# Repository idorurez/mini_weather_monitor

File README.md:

# Amefuriko — Mini Weather Monitor

After using a really crappy indoor temp and humidity monitor, I wanted to build one for myself to see if I could do better. This is the result. Is it better? I have no idea, but at least it also has a forecast I can trust, built the way I like.

## What it does

* Indoor temperature (°F), humidity, and pressure from a BME280, refreshed every 60 seconds
* Date and time, synced over NTP
* Two-day forecast from Weather Underground: today and tomorrow, with a big icon showing today's weather (sun, clouds, rain, etc.)
* Backlight that follows the room: a BH1750 ambient light sensor drives PWM with smooth ramping, no stepped jumps

## Hardware

* ESP32 devkit (ESP-WROOM-32)
* 4" 480x320 TFT, ST7796 over SPI, run in portrait (320x480)
* BME280 (temp / humidity / pressure) and BH1750 (ambient light) on I2C
* Micro SD card on its own VSPI bus
* Custom PCB and schematic in `pcb/` (KiCad), 3D-printed stand/case models in `model/` (SolidWorks)

Pin map lives in `src/User_Setup.h`. TFT on MOSI 13 / SCLK 14 / CS 15 / DC 26 / RST 32, backlight on GPIO 4 (PWM). SD on VSPI: MOSI 23 / MISO 19 / SCLK 18 / CS 5.

## SD card contents

Everything in `sdcard/` goes on the card root:

* `kozgoprobold*.vlw` — Kozuka Gothic Bold smooth fonts, the UI typeface
* `*_120x120.jpg` — weather icons, named by Weather Underground icon code
* `weather.cfg` — your secrets and location (below). Not in the repo on purpose.

## Configuration

`/weather.cfg` on the SD card, JSON:

```json
{
  "wu_api_key": "your weather underground key",
  "zip": "94070",
  "station_id": "",
  "WIFI": { "hostname": "yokai", "ssid": "your-ssid", "pass": "your-password" },
  "LOCATION": { "latitude": "37.50", "longitude": "-122.34" }
}
```

## Build and flash

PlatformIO project (`platformio.ini` targets `esp32dev`, Arduino framework). Build and upload from VS Code with PlatformIO, or:

```
pio run -t upload
```

Serial monitor at 115200 baud.

## Layout

* `src/` — firmware
* `pcb/` — KiCad schematic and PCB
* `model/` — SolidWorks case/stand models plus a gcode
* `sdcard/` — fonts, weather icons, and config that live on the SD card

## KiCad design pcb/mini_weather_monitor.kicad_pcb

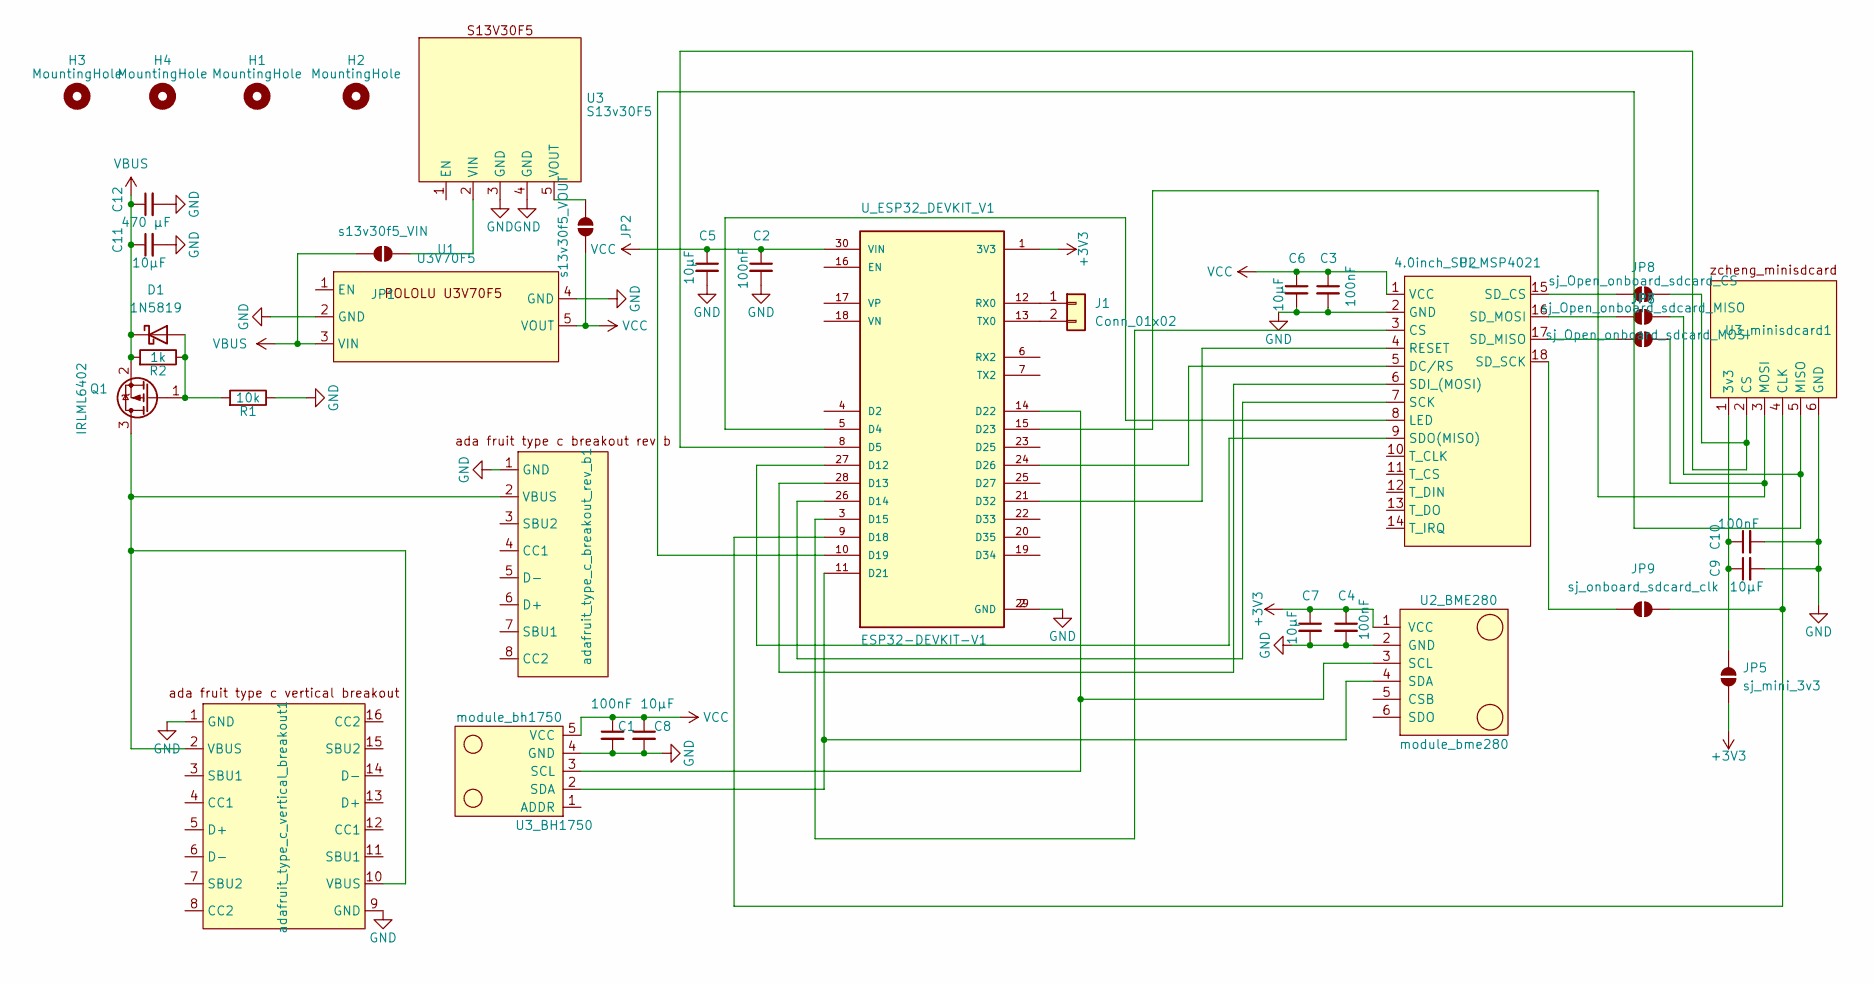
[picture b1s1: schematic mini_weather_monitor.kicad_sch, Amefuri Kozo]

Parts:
C1, C2, C3, C4, C10: 100nF; C_1206_3216Metric_Pad1.33x1.80mm_HandSolder
C5, C6, C7, C8, C9, C11: 10µF; C_1206_3216Metric_Pad1.33x1.80mm_HandSolder
C12: 470 µF; C_1206_3216Metric_Pad1.33x1.80mm_HandSolder
D1: 1N5819; D_SOD-123
H1, H2, H3, H4: MountingHole; MountingHole_2.2mm_M2
J1: Conn_01x02; PinHeader_1x02_P2.54mm_Vertical
JP1: s13v30f5_VIN; SolderJumper-2_P1.3mm_Open_RoundedPad1.0x1.5mm
JP2: s13v30f5_VOUT; SolderJumper-2_P1.3mm_Open_RoundedPad1.0x1.5mm
JP5: sj_mini_3v3; SolderJumper-2_P1.3mm_Open_RoundedPad1.0x1.5mm
JP6: sj_Open_onboard_sdcard_MOSI; SolderJumper-2_P1.3mm_Open_RoundedPad1.0x1.5mm
JP7: sj_Open_onboard_sdcard_MISO; SolderJumper-2_P1.3mm_Open_RoundedPad1.0x1.5mm
JP8: sj_Open_onboard_sdcard_CS; SolderJumper-2_P1.3mm_Open_RoundedPad1.0x1.5mm
JP9: sj_onboard_sdcard_clk; SolderJumper-2_P1.3mm_Open_RoundedPad1.0x1.5mm
Q1: IRLML6402; SOT-23
R1: 10k; R_1206_3216Metric
R2: 1k; R_1206_3216Metric
U1: U3V70F5; Pololu U3V70F5
U2: 4.0inch_SPI_MSP4021; 4.0inch_SPI
U2_BME280: module_bme280
U3: S13v30F5; pololu S13V30F5 step up step down
U3_BH1750: module_bh1750
U3_minisdcard1: zicheng_mini_sd_card_reader
U_ESP32_DEVKIT_V1: ESP32-DEVKIT-V1; MODULE_ESP32_DEVKIT_V1; PARTREV N/A
adafruit_type_c_breakout_rev_b1: Adafruit_USB_Type_C_Breakout_rev_B
adafruit_type_c_vertical_breakout1: Adafruit_USB_Type_C_Vertical_Breakout

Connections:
+3V3: C4.1, C7.1, JP5.1 (A), U2_BME280.1 (VCC), U_ESP32_DEVKIT_V1.1 (3V3)
GND: C1.2, C2.2, C3.2, C4.2, C5.2, C6.2, C7.2, C8.2, C9.2, C10.2, C11.2, C12.2, R1.1, U1.2 (GND), U1.4 (GND), U2.2 (GND), U2_BME280.2 (GND), U3.3 (GND), U3.4 (GND), U3_BH1750.4 (GND), U3_minisdcard1.6 (GND), U_ESP32_DEVKIT_V1.2 (GND), U_ESP32_DEVKIT_V1.29 (GND), adafruit_type_c_breakout_rev_b1.1 (GND), adafruit_type_c_vertical_breakout1.1 (GND), adafruit_type_c_vertical_breakout1.9 (GND)
unnamed: D1.2 (A), Q1.1 (G), R1.2, R2.1
unnamed: J1.1, U_ESP32_DEVKIT_V1.12 (RX0)
unnamed: J1.2, U_ESP32_DEVKIT_V1.13 (TX0)
unnamed: JP1.1 (A), U3.2 (VIN)
unnamed: JP2.1 (A), U3.5 (VOUT)
unnamed: C9.1, C10.1, JP5.2 (B), U3_minisdcard1.1 (3v3)
unnamed: JP6.1 (A), U2.16 (SD_MOSI)
unnamed: JP6.2 (B), U3_minisdcard1.5 (MISO), U_ESP32_DEVKIT_V1.10 (D19)
unnamed: JP7.1 (A), U2.17 (SD_MISO)
unnamed: JP7.2 (B), U3_minisdcard1.3 (MOSI), U_ESP32_DEVKIT_V1.15 (D23)
unnamed: JP8.1 (A), U2.15 (SD_CS)
unnamed: JP8.2 (B), U3_minisdcard1.2 (CS), U_ESP32_DEVKIT_V1.8 (D5)
unnamed: JP9.1 (A), U2.18 (SD_SCK)
unnamed: JP9.2 (B), U3_minisdcard1.4 (CLK), U_ESP32_DEVKIT_V1.9 (D18)
unnamed: Q1.3 (D), adafruit_type_c_breakout_rev_b1.2 (VBUS), adafruit_type_c_vertical_breakout1.2 (VBUS), adafruit_type_c_vertical_breakout1.10 (VBUS)
unnamed: U2.3 (CS), U_ESP32_DEVKIT_V1.3 (D15)
unnamed: U2.5 (DC/RS), U_ESP32_DEVKIT_V1.24 (D26)
unnamed: U2.8 (LED), U_ESP32_DEVKIT_V1.5 (D4)
unnamed: U2.4 (RESET), U_ESP32_DEVKIT_V1.21 (D32)
unnamed: U2.7 (SCK), U_ESP32_DEVKIT_V1.26 (D14)
unnamed: U2.6 (SDI_(MOSI)), U_ESP32_DEVKIT_V1.28 (D13)
unnamed: U2.9 (SDO(MISO)), U_ESP32_DEVKIT_V1.27 (D12)
unnamed: U2_BME280.3 (SCL), U3_BH1750.3 (SCL), U_ESP32_DEVKIT_V1.14 (D22)
unnamed: U2_BME280.4 (SDA), U3_BH1750.2 (SDA), U_ESP32_DEVKIT_V1.11 (D21)
VBUS: C11.1, C12.1, D1.1 (K), JP1.2 (B), Q1.2 (S), R2.2, U1.3 (VIN)
VCC: C1.1, C2.1, C3.1, C5.1, C6.1, C8.1, JP2.2 (B), U1.5 (VOUT), U2.1 (VCC), U3_BH1750.5 (VCC), U_ESP32_DEVKIT_V1.30 (VIN)

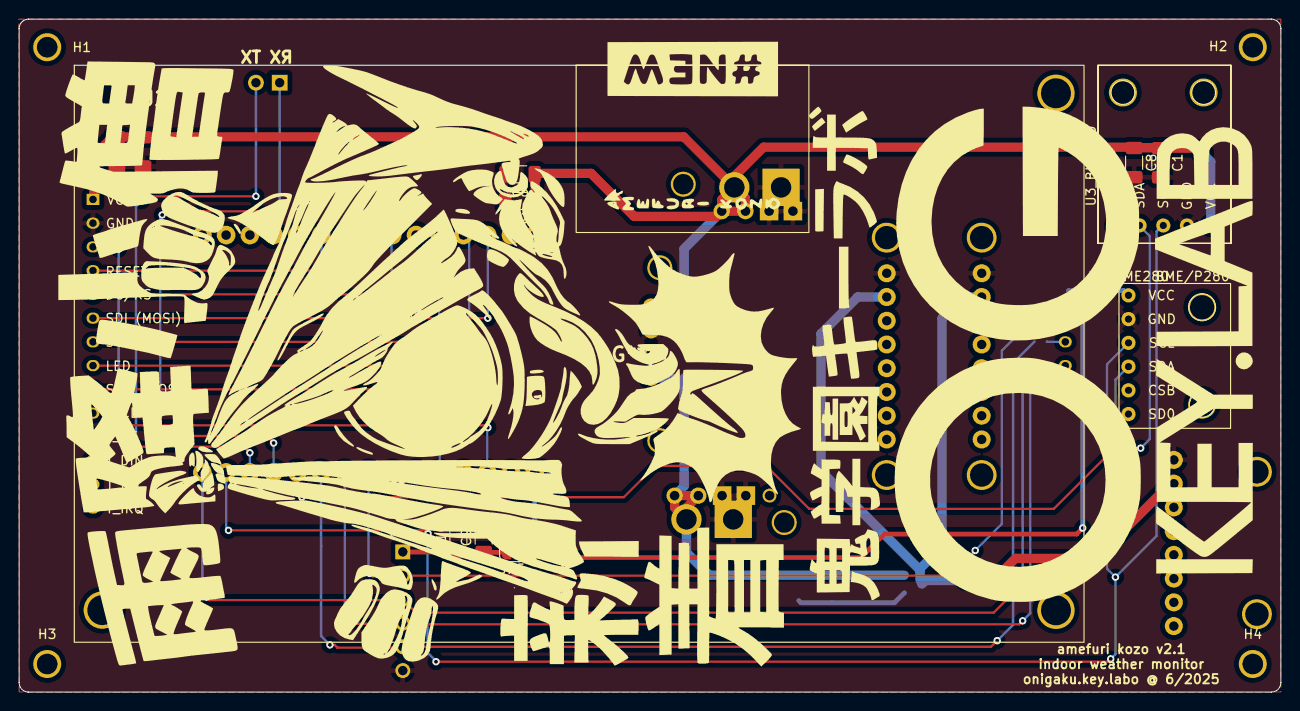
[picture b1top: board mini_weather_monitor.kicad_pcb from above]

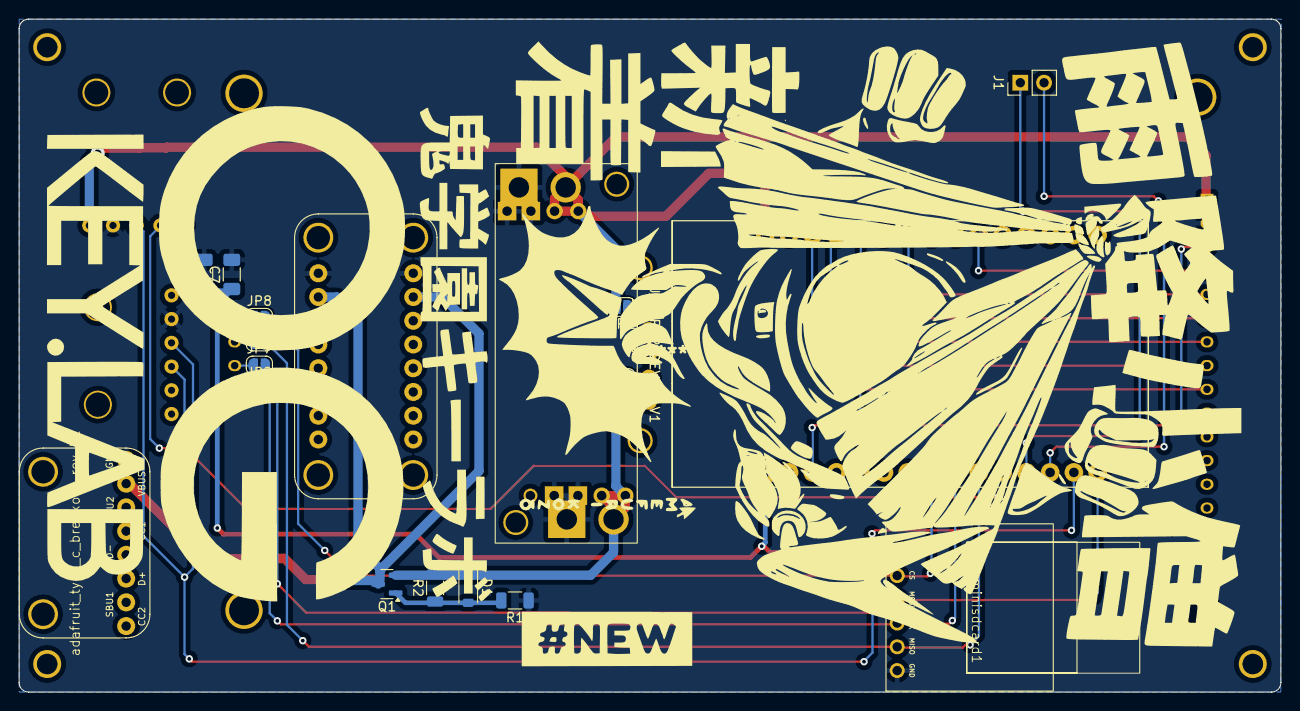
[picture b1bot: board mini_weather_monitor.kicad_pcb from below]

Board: 2 copper layers, 135.0 x 72.0 mm, 35 parts (19 on the bottom side), 28 nets.

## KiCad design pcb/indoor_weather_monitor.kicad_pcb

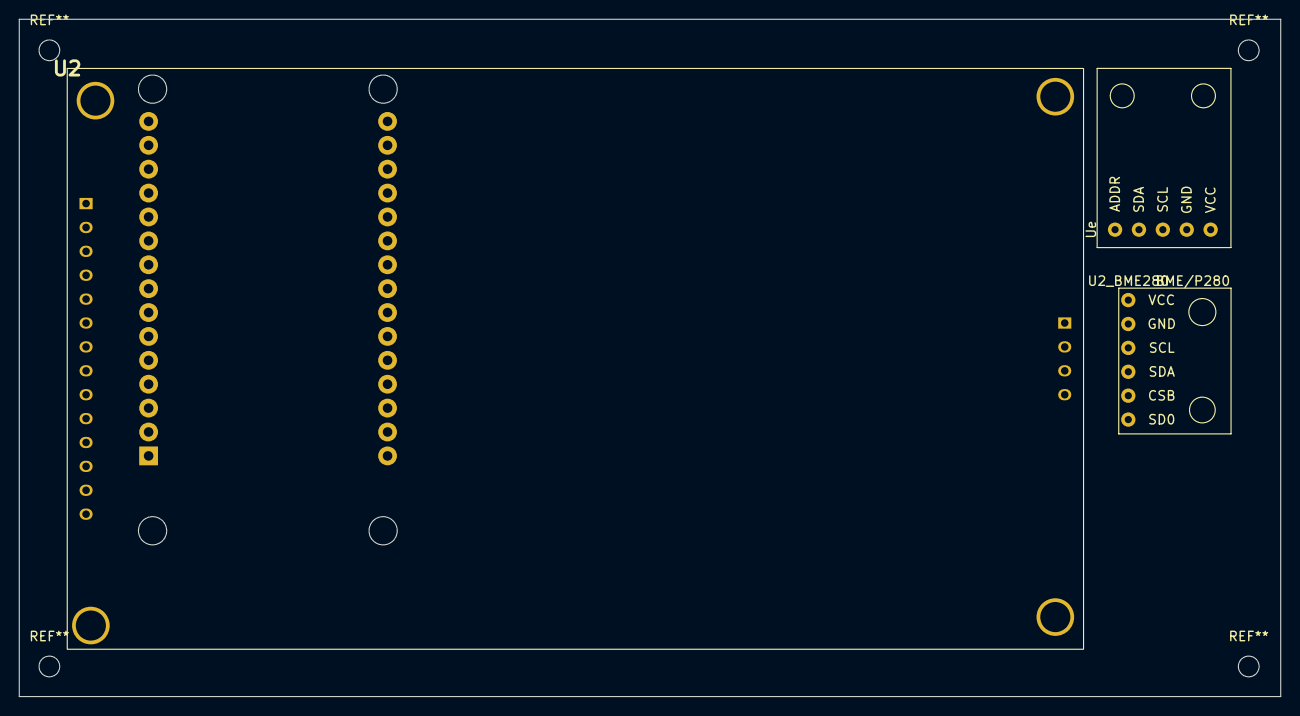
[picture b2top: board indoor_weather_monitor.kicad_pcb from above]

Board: 2 copper layers, 134.1 x 72.0 mm, 4 parts (1 on the bottom side), 11 nets, no tracks yet.

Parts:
U1: DOIT-ESP32-DEVKIT-V1; MODULE_ESP32_DEVKIT_V1
U2: 4.0inch_SPI_MSP4021; 4.0inch_SPI
U2_BME280: module_bme280
Ue: module_bh1750

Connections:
GND: U1.17 (GND), U2.2 (GND), U2_BME280.2 (GND), Ue.4 (GND)
unnamed: U1.6 (GPIO32_ADC1-CH4_RTC-GPIO9), U2.4 (RESET)
unnamed: U1.7 (GPIO33_ADC1-CH5_RTC-GPIO8), U2.3 (CS)
unnamed: U1.9 (GPIO26_ADC2-CH9_DAC2_RTC-GPIO7), U2.5 (DC/RS)
unnamed: U1.18 (VIN), U2.1 (VCC), Ue.5 (VCC)
unnamed: U1.19 (3V3), U2_BME280.1 (VCC)
unnamed: U1.24 (GPIO15_ADC2-CH3_HSPI-CS0_RTC-GPIO13), U2_BME280.5 (CSB)
unnamed: U1.26 (GPIO4_ADC2-CH0_RTC-GPIO10), U2.8 (LED)
unnamed: U1.30 (GPIO18_VSPI-CLK), U2.7 (SCK), U2_BME280.3 (SCL), Ue.3 (SCL)
unnamed: U2.9 (SDO(MISO)), U2_BME280.6 (SDO)
unnamed: U2.6 (SDI_(MOSI)), U2_BME280.4 (SDA)

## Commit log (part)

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2021-11-21 wip on adding icons
2021-11-22 wip jpeg decoder
2021-11-25 wip connecting to wu or another service
2021-11-27 wip crash
2021-11-28 working bme display and call to forecast
2021-12-14 futzing with text sizing
2022-01-02 added readme and stuff
2022-01-02 readme updates
2022-01-03 adding mined licons, fixing formatting, wip
2022-01-04 forecast gui update, fonts, and text placement
2022-01-05 adding bh1750 to sense light to dim lcd. moved a pin or two to accommodate i2c
2022-01-06 working on separate current conditions display
2022-01-13 tooling around with placement
2022-01-13 draw upates
2022-01-15 repositioning local forecast
2022-01-24 updated pcb and everything is working so far
2022-01-27 readding src
2022-01-27 wip debug sdcard vs spiffs artifacting
2022-02-14 wip, with MPU6050, but will switch to SW520D
2022-03-11 fixing orientation with new tilt sensor and adding libraries to repo
2022-06-02 fixxing footprint and pad
2022-06-02 fixxing footprint on power supply
2022-06-02 trace cleanup
2022-06-03 updated silkscreen placement and fixes
2022-06-20 fixing tilt sensor and power connection was not updated from library
2022-07-02 working after pcb
2022-08-03 latest with 2 degree adjustment
2022-08-10 wip on figuring out freeze
2022-08-18 adding watchdog to reset
2022-09-05 updated secrets
2022-09-05 untracked secrets
2024-09-20 working pass, colors, tbd on time bug stop
2024-09-28 stripped and rebuilt working
2024-10-28 revamping a bit
2024-10-31 adding extra usb input
2024-11-06 using adafruit stuff
2024-11-07 adding caps and diodes
2025-03-01 working code. pcb wip
2025-03-02 set mosfet, schottkey and resistor
2025-03-21 adding mini sdcard to use instead of onboard sdcard
2025-04-29 moved config info to config on sdcard
2025-05-01 updated to use struct
2025-05-03 fixing mosfet setup, also updating for day of the week length
2025-06-05 added fonts
2025-06-05 adding passthrough
2025-06-14 slight retrace
2025-06-16 fixing forecast parsing and display
2025-06-27 changed colors, updated pcb
2025-11-12 set font size based on length of month/day
